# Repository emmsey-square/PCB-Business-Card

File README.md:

#   PCB Business Card- A Business Card to Help Me Stand Out

## Brief 
I've seen online heaps of people in the hobbyist/engineering field design their own business cards/badges to  give out to people, and I wnated to make one of my own to help me stand out among my peers.

My spin on the PCB business card is a simple 1D Pong game; there's a string of LED's between two pushbutton switches, with one LED lighting up at a time and moving along the string in alternating directions. When the LED reaches the end of the string, the player must press the button on that side to 'swat' it away, otherwise they will lose 1 of their 3 lives. Each successful swat increases the speed of the LED movement, until eventually it's impossible to win. Additionally, holding the buttons the whole time (AKA cheating) results in a loss of a life. Losing all lives results in game over. 
## Design Choices 
- Utilising a CH32V003 for my main mcu, as it is a cheap 32-bit RISCV chip with plenty of peripherals and IO for a business card. I have an interest in the RISCV ISA, and there's a huge open source community around this chip mainly thanks to cnlohr and his [ch32fun SDK](https://github.com/cnlohr/ch32fun) 
- USB-C port port mainstream compatibility, although people will be understandably hesitant to plug this into things
- Onboard passive buzzer for sound effects (work in progress)

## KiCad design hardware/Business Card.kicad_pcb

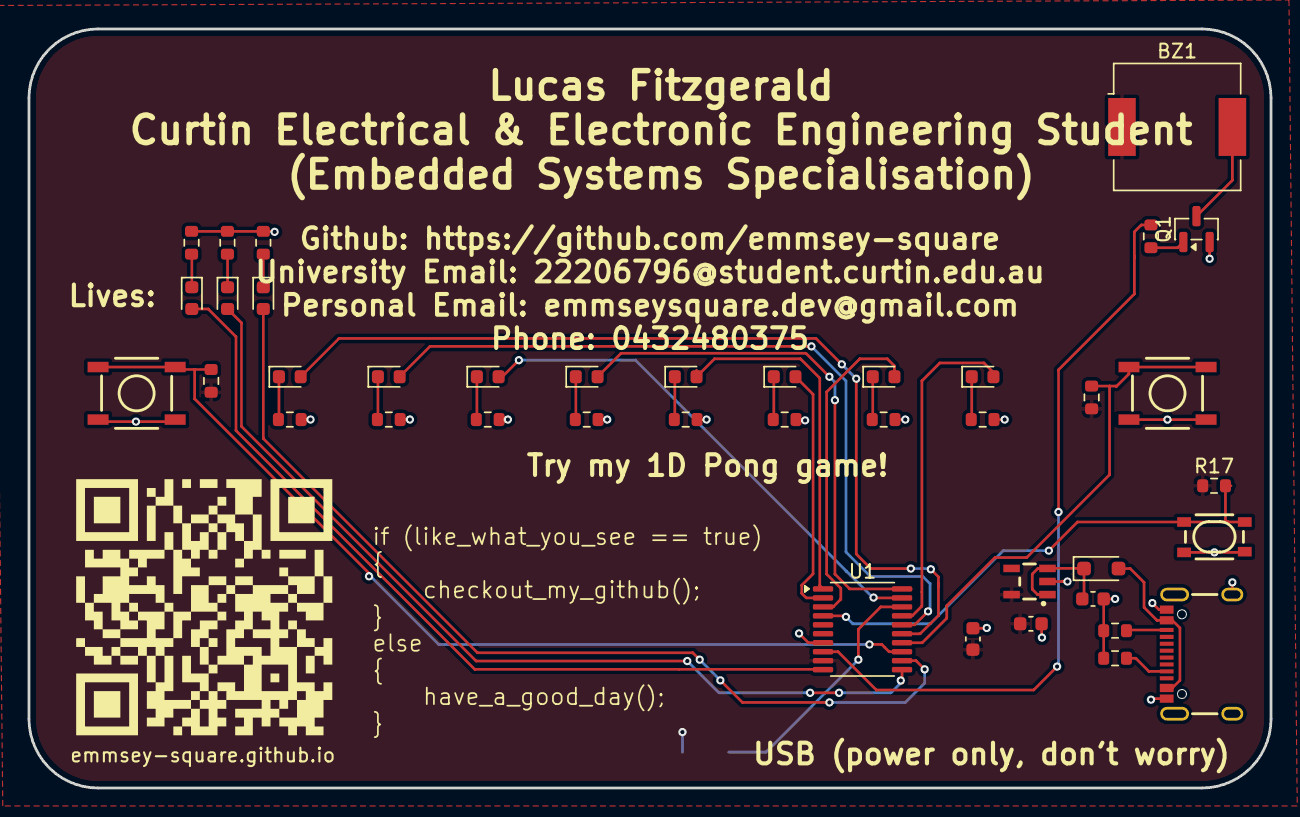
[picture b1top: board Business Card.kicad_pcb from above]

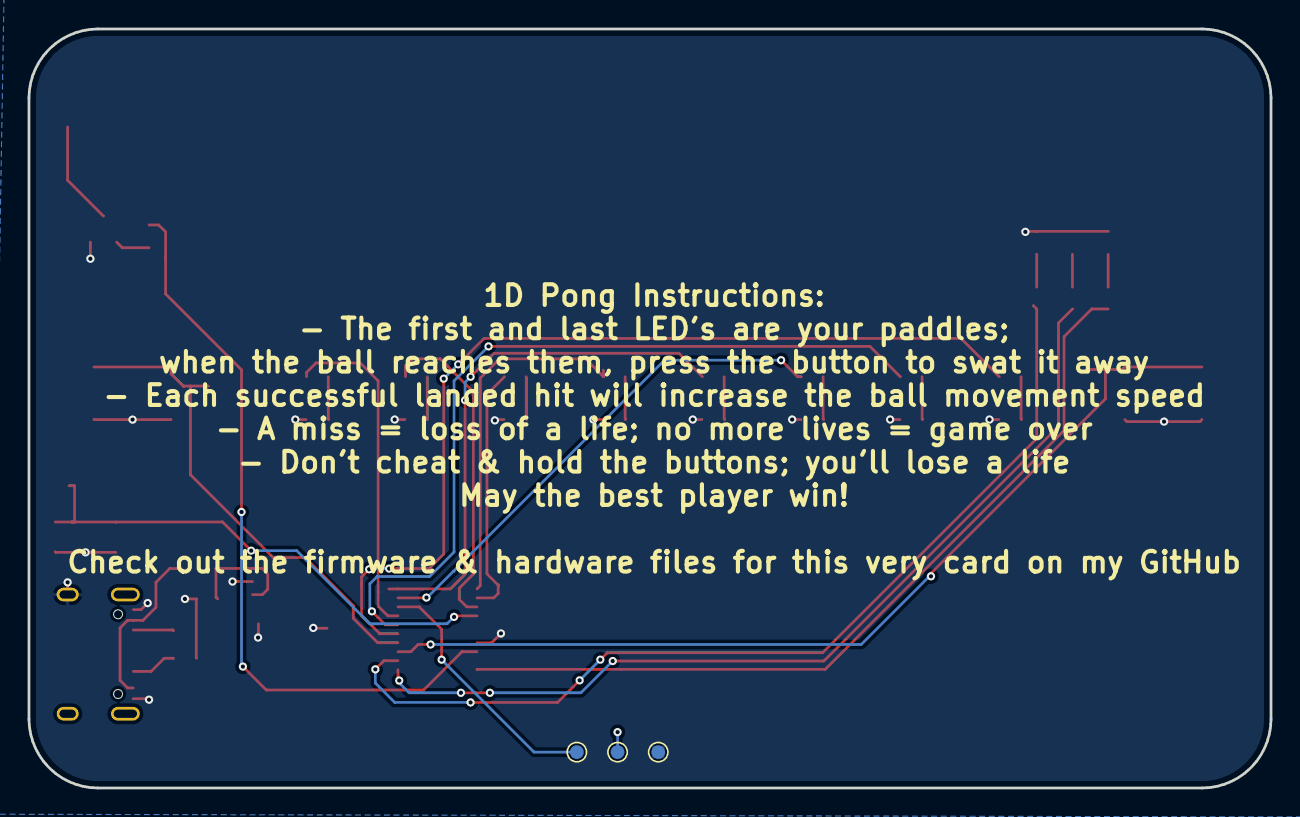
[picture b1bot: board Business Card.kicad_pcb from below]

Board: 2 copper layers, 90.0 x 55.0 mm, 43 parts (3 on the bottom side), 35 nets.

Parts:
BZ1: Buzzer; Buzzer_CUI_CPT-9019S-SMT
C1: 0.1u; C_0603_1608Metric
C2: 1u; C_0603_1608Metric
C3: 10u; C_0603_1608Metric
D1, D2, D3, D4, D5, D6, D7, D8, D10, D11, D12: LED; LED_0603_1608Metric
D9: 1N5819WS; D_SOD-323_HandSoldering
J1: USB_C_Receptacle; USB-C_16
Q1: BC847; SOT-23
R1, R2, R17: 10k; R_0603_1608Metric
R3, R4: 5.1k; R_0603_1608Metric
R5, R6, R7, R8, R9, R10, R11, R12, R13, R14, R15, R16: R; R_0603_1608Metric
SW1, SW2: SMD_5.2x5.2mm_h1.9mm; Push_SMD_5.2x5.2mm_h1.9mm
SW3: SMD_4.2x3.2mm_h2.5mm; Push_SMD_4.2x3.2mm
TP1: SWIO; TestPoint_Pad_D1.0mm
TP2: 3.3V; TestPoint_Pad_D1.0mm
TP3: GND; TestPoint_Pad_D1.0mm
U1: CH32V003FxPx; TSSOP-20_4.4x6.5mm_P0.65mm
U2: RT9080-3.3; SOT23-5

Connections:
+3.3V: BZ1.1 (+), C1.1, C3.1, R1.1, R2.1, R17.1, TP2.1, U1.9 (VDD), U2.5 (VOUT)
/BZR: R16.1, U1.8 (PD0)
/D0: D1.2 (A), U1.15 (PC5)
/D1: D2.2 (A), U1.16 (PC6)
/D2: D3.2 (A), U1.19 (PD2)
/D3: D4.2 (A), U1.20 (PD3)
/D4: D5.2 (A), U1.1 (PD4)
/D5: D6.2 (A), U1.2 (PD5)
/D6: D7.2 (A), U1.3 (PD6)
/D7: D8.2 (A), U1.17 (PC7)
/D10: D10.2 (A), U1.10 (PC0)
/D11: D11.2 (A), U1.11 (PC1)
/D12: D12.2 (A), U1.12 (PC2)
/NRST: R17.2, SW3.1, U1.4 (PD7)
/SW1: R1.2, SW1.1, U1.13 (PC3)
/SW2: R2.2, SW2.1, U1.14 (PC4)
/SWIO: TP1.1, U1.18 (PD1)
GND: C1.2, C2.2, C3.2, J1.GND, J1.S (SHIELD), Q1.2 (E), R3.2, R4.2, R5.2, R6.2, R7.2, R8.2, R9.2, R10.2, R11.2, R12.2, R13.2, R14.2, R15.2, SW1.2, SW2.2, SW3.2, TP3.1, U1.7 (VSS), U2.2 (GND)
unnamed: BZ1.2 (-), Q1.3 (C)
unnamed: D1.1 (K), R5.1
unnamed: D2.1 (K), R6.1
unnamed: D3.1 (K), R7.1
unnamed: D4.1 (K), R8.1
unnamed: D5.1 (K), R9.1
unnamed: D6.1 (K), R10.1
unnamed: D7.1 (K), R11.1
unnamed: D8.1 (K), R12.1
unnamed: D9.2 (A), J1.VBUS
unnamed: C2.1, D9.1 (K), U2.1 (VIN), U2.3 (EN)
unnamed: D10.1 (K), R13.1
unnamed: D11.1 (K), R14.1
unnamed: D12.1 (K), R15.1
unnamed: J1.A5 (CC1), R3.1
unnamed: J1.B5 (CC2), R4.1
unnamed: Q1.1 (B), R16.2

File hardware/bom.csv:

"Id";"Designator";"Footprint";"Quantity";"Designation";"Supplier and ref";
1;"J1";"USB-C_16";1;"USB_C_Receptacle";;;
2;"R13,R8,R10,R9,R5,R7,R11,R12,R15,R14,R6";"R_0603_1608Metric";11;"R";;;
3;"R3,R4";"R_0603_1608Metric";2;"5.1k";;;
4;"Q1";"SOT-23";1;"BC847";;;
5;"D5,D4,D1,D3,D12,D7,D2,D8,D11,D10,D6";"LED_0603_1608Metric";11;"LED";;;
6;"U1";"TSSOP-20_4.4x6.5mm_P0.65mm";1;"CH32V003FxPx";;;
7;"BZ1";"Buzzer_CUI_CPT-9019S-SMT";1;"Buzzer";;;
8;"R17,R1,R2";"R_0603_1608Metric";3;"10k";;;
9;"SW3";"Push_SMD_4.2x3.2mm";1;"SMD_4.2x3.2mm_h2.5mm";;;
10;"SW2,SW1";"Push_SMD_5.2x5.2mm_h1.9mm";2;"SMD_5.2x5.2mm_h1.9mm";;;
11;"C3";"C_0603_1608Metric";1;"10u";;;
12;"D9";"D_SOD-323_HandSoldering";1;"1N5819WS";;;
13;"R16";"R_0603_1608Metric";1;"R";;;
14;"C1";"C_0603_1608Metric";1;"0.1u";;;
15;"U2";"SOT23-5";1;"RT9080-3.3";;;
16;"C2";"C_0603_1608Metric";1;"1u";;;
17;"TP3";"TestPoint_Pad_D1.0mm";1;"GND";;;
18;"TP1";"TestPoint_Pad_D1.0mm";1;"SWIO";;;
19;"TP2";"TestPoint_Pad_D1.0mm";1;"3.3V";;;

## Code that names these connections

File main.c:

#include "../ch32fun/ch32fun.h"
#include "funconfig.h"

/*

Buttons: PD5:6	
LED strip: PC0:7
Life LED's: PD4, PA1:2
*/

//uint8_t ledStrip[8] = {PC0, PC1, PC2, PC3, PC4, PC5, PC6, PC7};
//uint8_t lifeLeds[3] = {PD4, PA1, PA2};

#define LED_PIN	PA2


uint8_t ledStrip[8] = {PD0, PD1, PD2, PD3, PD4, PD5, PD6, PD7};
uint8_t lifeLeds[3] = {PD4, PA1, PA2};

int main(void)
{
	SystemInit();
	funGpioInitAll();

	//funPinMode(PC0, GPIO_Speed_10MHz | GPIO_CNF_OUT_PP);
	
	//funPinMode(PA2, GPIO_Speed_In | GPIO_CNF_IN_FLOATING);
	
	for (int i = 0; i < 8; i++)
	{
		funPinMode(ledStrip[i], GPIO_Speed_10MHz | GPIO_CNF_OUT_PP);
	}


	while(1)
	{
		//uint8_t input = funDigitalRead(PA2);

		//funDigitalWrite(PC0, input);

		for (int i = 0; i < 8; i++)
		{
			funDigitalWrite(ledStrip[i], FUN_HIGH);
			Delay_Ms(250);
		}

		for (int i = 0; i < 8; i++)
		{
			funDigitalWrite(ledStrip[i], FUN_LOW);
		}
		
	}

	return 0;
}

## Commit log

2026-01-15 added Makefile, funconfig.h, main.c
2026-01-15 moved src files to firmware folder
2026-01-15 updated main.c
2026-01-17 fixed gitignore
2026-01-18 updated main.c and funconfig.h
2026-01-19 updated main.c, lives functionality in progress
2026-01-19 updated main.c, implemented lives functionality mostly, working out bugs in determing if game has started or not
2026-01-19 updated main.c, lives decrement properly after first round
2026-01-22 fixed simulatneous button press bug, losing all lives results in game over
2026-01-24 Added kicad hardware files, gerbers & bom
2026-03-26 Added business card images
